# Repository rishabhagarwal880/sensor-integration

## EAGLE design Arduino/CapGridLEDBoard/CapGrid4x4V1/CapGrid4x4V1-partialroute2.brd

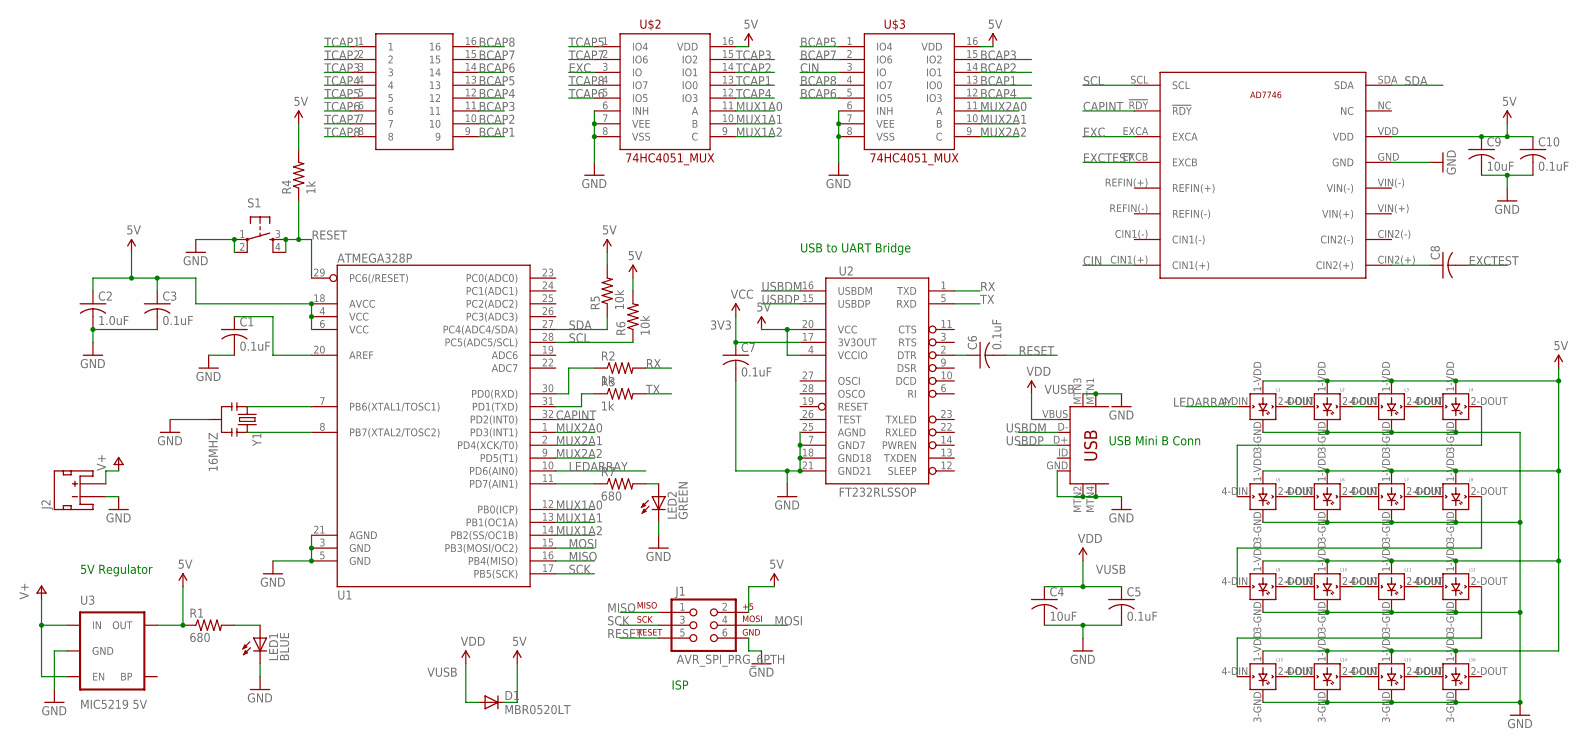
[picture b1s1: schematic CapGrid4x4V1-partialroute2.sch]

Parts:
C1, C3, C5, C6, C7, C10: 0.1uF; C0805K; MPN 08055C104KAZ2A
C2: 1.0uF; C0805K; MPN C0805C105M4RACTU
C4, C9: 10uF; C0805K; MPN C2012X5R1A106K125AB
C8: C-US025-025X050; C025-025X050
D1: MBR0520LT; SOD123; MPN MBR0520LT1G
J1: AVR_SPI_PRG_6PTH; 2X3
J2: JST_2MM_MALE; JST-2-SMD; MPN S2B-PH-SM4-TB(LF)(SN)
L1, L2, L3, L4, L5, L6, L7, L8, L9, L10, L11, L12, L13, L14, L15, L16: WS2812B
LED1: BLUE; CHIP-LED0805; MPN CMD17-21VRC/TR8
LED2: GREEN; CHIP-LED0805; MPN CMD17-21VGC/TR8
R1, R7: 680; R0805; MPN ERJ-6ENF6800V
R2, R3, R4: 1k; R0805; MPN CRCW08051K00FKTA
R5, R6: 10k; R0805; MPN CRCW080510K0FKEA
S1: TAC_SWITCHSMD; TACTILE-SWITCH-SMD; MPN MC32845
U1: ATMEGA328P; TQFP32-08; MPN ATMEGA328P-AU
U2: FT232RLSSOP; SSOP28DB; MPN FT232RL
U3: MIC5219 5V; SOT23-5
U$1: USB-MINIB-5PIN; USB-MINIB; MPN 67503-1230
U$2, U$3: 74HC4051_MUX; SO16
U$4: AD7746; MPN AD7746ARUZ
U$5: CAP8CONN
Y1: 16MHZ; RESONATOR-SMD; MPN PBRC16.00MR70X000

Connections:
3V3: C7.1, U2.17 (3V3OUT)
5V: C2.1, C3.1, C9.1, C10.1, D1.C, J1.2, L1.1-VDD (VDD), L2.1-VDD (VDD), L3.1-VDD (VDD), L4.1-VDD (VDD), L5.1-VDD (VDD), L6.1-VDD (VDD), L7.1-VDD (VDD), L8.1-VDD (VDD), L9.1-VDD (VDD), L10.1-VDD (VDD), L11.1-VDD (VDD), L12.1-VDD (VDD), L13.1-VDD (VDD), L14.1-VDD (VDD), L15.1-VDD (VDD), L16.1-VDD (VDD), R1.1, R4.2, R5.2, R6.2, U1.4 (VCC), U1.6 (VCC), U1.18 (AVCC), U2.4 (VCCIO), U2.20 (VCC), U3.5 (OUT), U$2.16 (VDD), U$3.16 (VDD), U$4.VDD
BCAP1: U$3.13 (IO0), U$5.9
BCAP2: U$3.14 (IO1), U$5.10
BCAP3: U$3.15 (IO2), U$5.11
BCAP4: U$3.12 (IO3), U$5.12
BCAP5: U$3.1 (IO4), U$5.13
BCAP6: U$3.5 (IO5), U$5.14
BCAP7: U$3.2 (IO6), U$5.15
BCAP8: U$3.4 (IO7), U$5.16
CAPINT: U1.32 (PD2(INT0)), U$4.!RDY
CIN: U$3.3 (IO), U$4.CIN1(+)
EXC: U$2.3 (IO), U$4.EXCA
EXCTEST: C8.2, U$4.EXCB
GND: C1.2, C2.2, C3.2, C4.2, C5.2, C7.2, C9.2, C10.2, J1.6, J2.1 (-), L1.3-GND (GND), L2.3-GND (GND), L3.3-GND (GND), L4.3-GND (GND), L5.3-GND (GND), L6.3-GND (GND), L7.3-GND (GND), L8.3-GND (GND), L9.3-GND (GND), L10.3-GND (GND), L11.3-GND (GND), L12.3-GND (GND), L13.3-GND (GND), L14.3-GND (GND), L15.3-GND (GND), L16.3-GND (GND), LED1.C, LED2.C, S1.1, S1.2, U1.3 (GND), U1.5 (GND), U1.21 (AGND), U2.7 (GND7), U2.18 (GND18), U2.21 (GND21), U2.25 (AGND), U3.2 (GND), U$1.GND, U$1.MTN1 (MTN2), U$1.MTN2 (MTN3), U$1.MTN3 (MTN1), U$1.MTN4, U$2.6 (INH), U$2.7 (VEE), U$2.8 (VSS), U$3.6 (INH), U$3.7 (VEE), U$3.8 (VSS), U$4.GND, Y1.2
LEDARRAY: L1.4-DIN (DIN), U1.10 (PD6(AIN0))
MISO: J1.1, U1.16 (PB4(MISO))
MOSI: J1.4, U1.15 (PB3(MOSI/OC2))
MUX1A0: U1.12 (PB0(ICP)), U$2.11 (A)
MUX1A1: U1.13 (PB1(OC1A)), U$2.10 (B)
MUX1A2: U1.14 (PB2(SS/OC1B)), U$2.9 (C)
MUX2A0: U1.1 (PD3(INT1)), U$3.11 (A)
MUX2A1: U1.2 (PD4(XCK/T0)), U$3.10 (B)
MUX2A2: U1.9 (PD5(T1)), U$3.9 (C)
unnamed: R2.1, U1.30 (PD0(RXD))
unnamed: C6.1, U2.2 (DTR)
unnamed: R3.1, U1.31 (PD1(TXD))
unnamed: U1.7 (PB6(XTAL1/TOSC1)), Y1.1
unnamed: R7.1, U1.11 (PD7(AIN1))
unnamed: U1.8 (PB7(XTAL2/TOSC2)), Y1.3
unnamed: C1.1, U1.20 (AREF)
unnamed: LED1.A, R1.2
unnamed: LED2.A, R7.2
unnamed: L4.2-DOUT (DOUT), L5.4-DIN (DIN)
unnamed: L10.2-DOUT (DOUT), L11.4-DIN (DIN)
unnamed: L1.2-DOUT (DOUT), L2.4-DIN (DIN)
unnamed: L2.2-DOUT (DOUT), L3.4-DIN (DIN)
unnamed: L3.2-DOUT (DOUT), L4.4-DIN (DIN)
unnamed: L5.2-DOUT (DOUT), L6.4-DIN (DIN)
unnamed: L6.2-DOUT (DOUT), L7.4-DIN (DIN)
unnamed: L7.2-DOUT (DOUT), L8.4-DIN (DIN)
unnamed: L8.2-DOUT (DOUT), L9.4-DIN (DIN)
unnamed: L9.2-DOUT (DOUT), L10.4-DIN (DIN)
unnamed: L11.2-DOUT (DOUT), L12.4-DIN (DIN)
unnamed: L12.2-DOUT (DOUT), L13.4-DIN (DIN)
unnamed: L13.2-DOUT (DOUT), L14.4-DIN (DIN)
unnamed: L14.2-DOUT (DOUT), L15.4-DIN (DIN)
unnamed: L15.2-DOUT (DOUT), L16.4-DIN (DIN)
unnamed: C8.1, U$4.CIN2(+)
RESET: C6.2, J1.5, R4.1, S1.3, S1.4, U1.29 (PC6(/RESET))
RX: R2.2, U2.1 (TXD)
SCK: J1.3, U1.17 (PB5(SCK))
SCL: R6.1, U1.28 (PC5(ADC5/SCL)), U$4.SCL
SDA: R5.1, U1.27 (PC4(ADC4/SDA)), U$4.SDA
TCAP1: U$2.13 (IO0), U$5.1
TCAP2: U$2.14 (IO1), U$5.2
TCAP3: U$2.15 (IO2), U$5.3
TCAP4: U$2.12 (IO3), U$5.4
TCAP5: U$2.1 (IO4), U$5.5
TCAP6: U$2.5 (IO5), U$5.6
TCAP7: U$2.2 (IO6), U$5.7
TCAP8: U$2.4 (IO7), U$5.8
TX: R3.2, U2.5 (RXD)
USBDM: U2.16 (USBDM), U$1.D-
USBDP: U2.15 (USBDP), U$1.D+
V+: J2.2 (+), U3.1 (IN), U3.3 (EN)
VUSB: C4.1, C5.1, D1.A, U$1.VBUS

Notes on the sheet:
5V Regulator
USB to UART Bridge
ISP
USB Mini B Conn

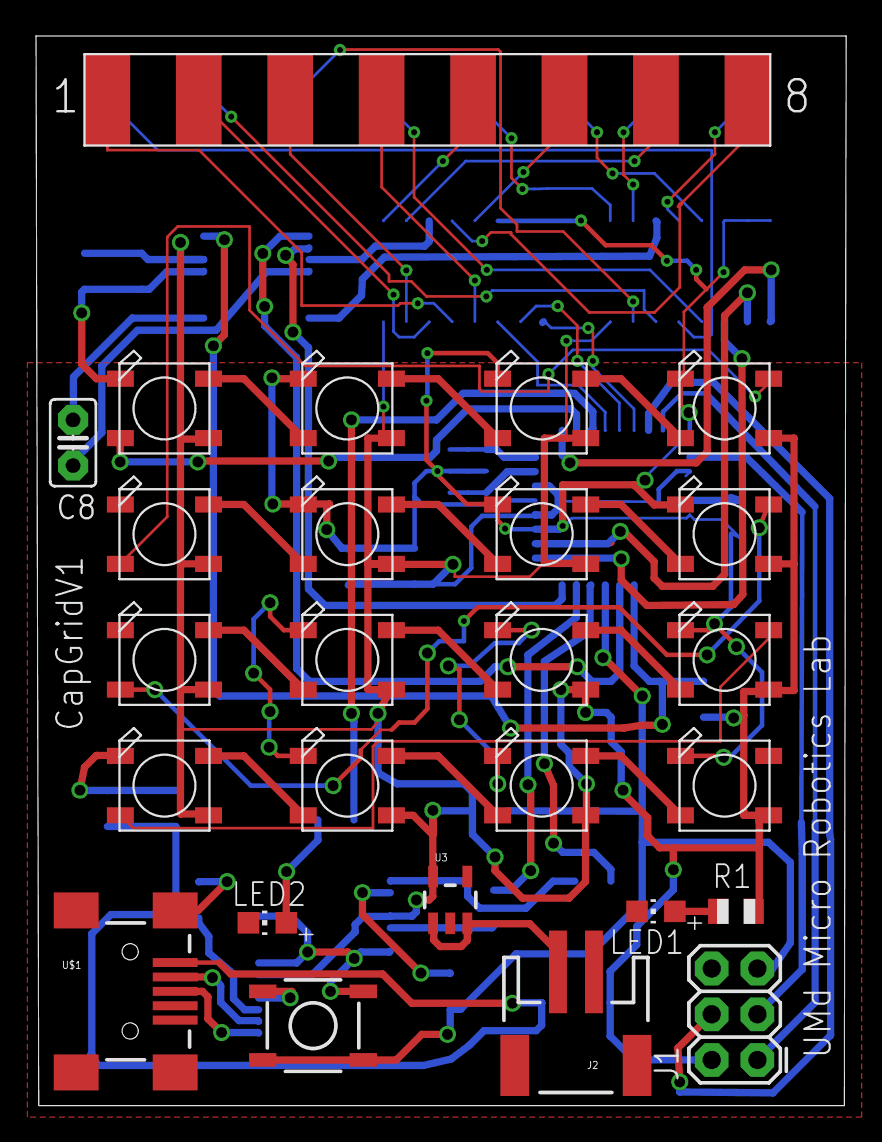
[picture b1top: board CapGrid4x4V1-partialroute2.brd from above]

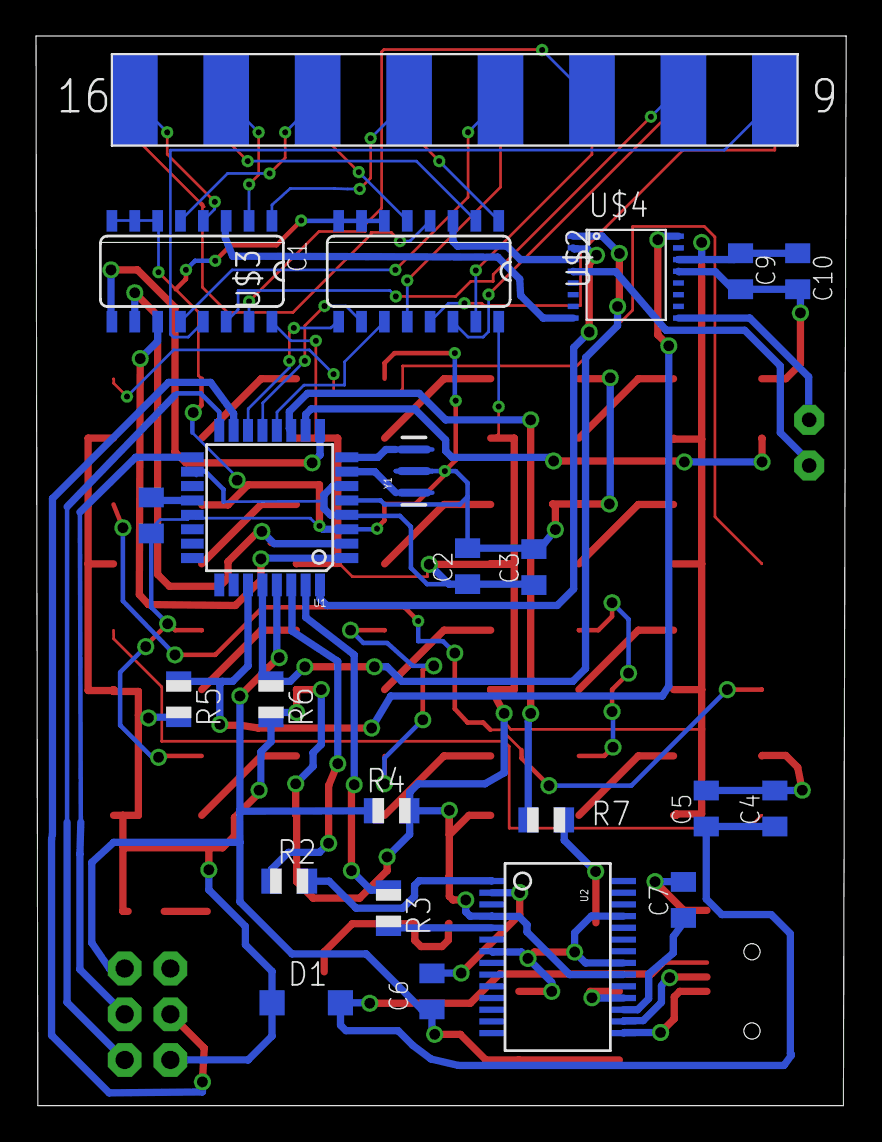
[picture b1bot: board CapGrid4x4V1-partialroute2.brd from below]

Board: 2 copper layers, 45.0 x 59.4 mm, 48 parts (22 on the bottom side), 67 nets.

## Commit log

2017-09-06 thesis repository created
2017-09-08 new sensor designs added
2017-09-08 Planarization code added
2017-09-11 acrylic mold updated for die shapes
2017-09-11 folder organized
2017-09-12 old design for alexi added
2017-09-18 updated the gcode
2017-09-18 350mm code edited
2017-09-20 code improved based on the cnc manufacturing
2017-09-20 sensor reading
2017-09-28 added the arduino code
2017-10-03 arduino files added
2017-10-04 arduino files updated
2017-10-04 gripper files updated
2017-10-04 new fils added for arduino and gripperwq
2017-10-09 circuit diagrams added for extention circuit
2017-10-18 flow square updated for compact design
2017-10-30 new design added
2017-11-02 arduino file updated and right hand file added
2017-11-03 force control added
2017-11-07 updated arduino communication
2017-11-09 baud rate corrected
2017-11-13 sensor gcode updated
2017-11-15 the ros arduino files duplicated for non ROS reading
2017-11-15 folder name updated
2017-11-15 folder structure improved

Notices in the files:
parts and their libraries:
SparkFun-DigitalIC: Licensing: Creative Commons ShareAlike 4.0 International - https://creativecommons.org/licenses/by-sa/4.0
